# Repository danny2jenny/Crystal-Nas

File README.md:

# Introduction

This is a NAS Case and extention pcb for NanoPi M4.

KiCAD for PCB and FreeCAD for case.

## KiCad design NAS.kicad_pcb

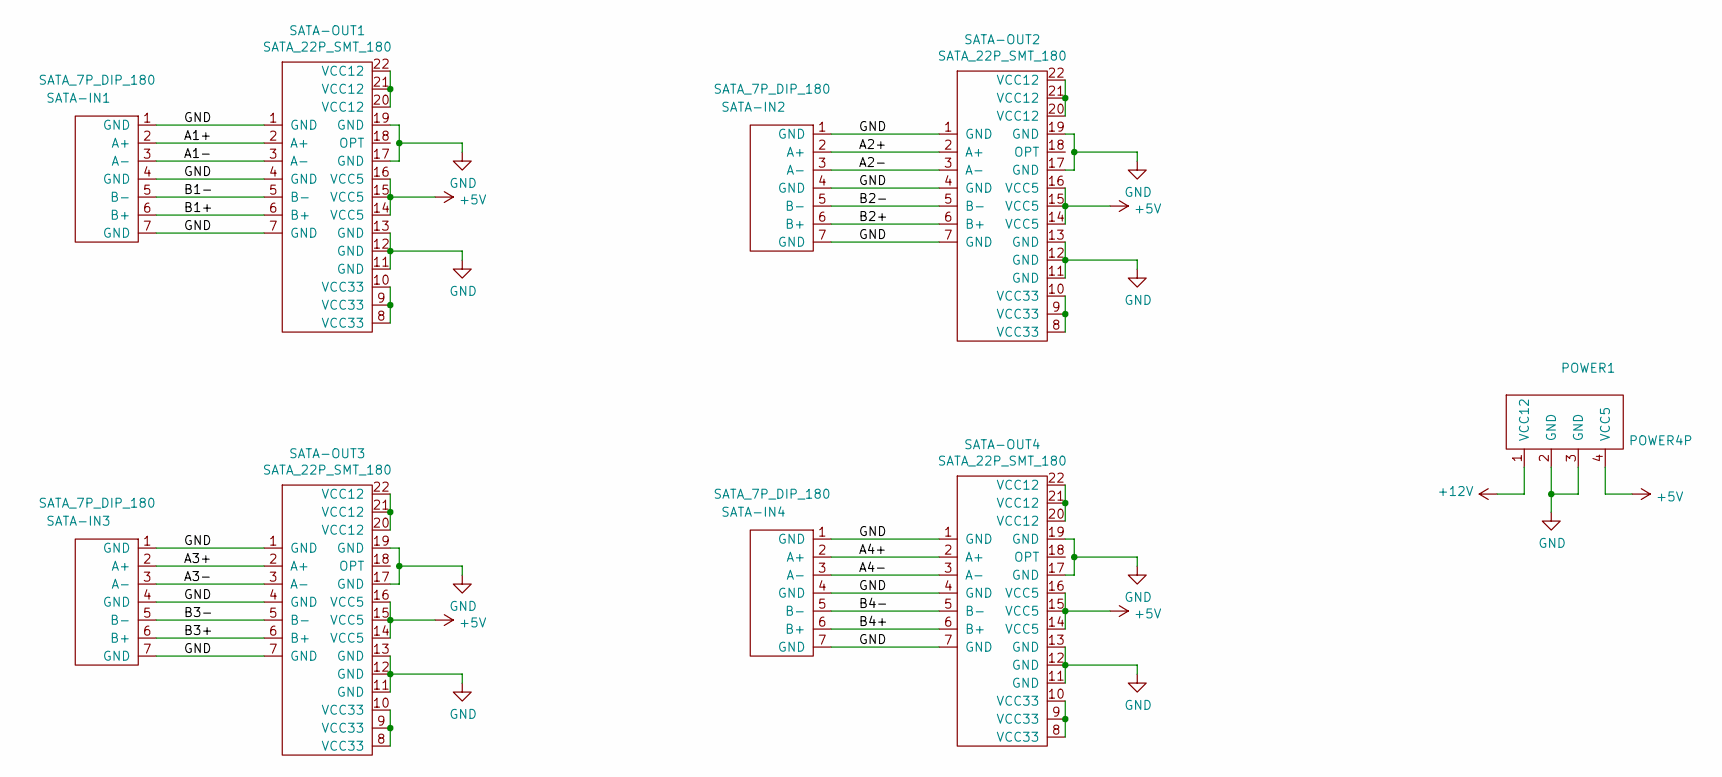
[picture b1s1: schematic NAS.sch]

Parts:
POWER1: POWER4P; Power4P
SATA-IN1, SATA-IN2, SATA-IN3, SATA-IN4: SATA_7P_DIP_180; SATA7PF180
SATA-OUT1, SATA-OUT2, SATA-OUT3, SATA-OUT4: SATA_22P_SMT_180; SATA715F9.1H

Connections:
+5V: POWER1.4 (VCC5), SATA-OUT1.14 (VCC5), SATA-OUT1.15 (VCC5), SATA-OUT1.16 (VCC5), SATA-OUT2.14 (VCC5), SATA-OUT2.15 (VCC5), SATA-OUT2.16 (VCC5), SATA-OUT3.14 (VCC5), SATA-OUT3.15 (VCC5), SATA-OUT3.16 (VCC5), SATA-OUT4.14 (VCC5), SATA-OUT4.15 (VCC5), SATA-OUT4.16 (VCC5)
+12V: POWER1.1 (VCC12)
/A1+: SATA-IN1.2 (A+), SATA-OUT1.2 (A+)
/A1-: SATA-IN1.3 (A-), SATA-OUT1.3 (A-)
/A2+: SATA-IN2.2 (A+), SATA-OUT2.2 (A+)
/A2-: SATA-IN2.3 (A-), SATA-OUT2.3 (A-)
/A3+: SATA-IN3.2 (A+), SATA-OUT3.2 (A+)
/A3-: SATA-IN3.3 (A-), SATA-OUT3.3 (A-)
/A4+: SATA-IN4.2 (A+), SATA-OUT4.2 (A+)
/A4-: SATA-IN4.3 (A-), SATA-OUT4.3 (A-)
/B1+: SATA-IN1.6 (B+), SATA-OUT1.6 (B+)
/B1-: SATA-IN1.5 (B-), SATA-OUT1.5 (B-)
/B2+: SATA-IN2.6 (B+), SATA-OUT2.6 (B+)
/B2-: SATA-IN2.5 (B-), SATA-OUT2.5 (B-)
/B3+: SATA-IN3.6 (B+), SATA-OUT3.6 (B+)
/B3-: SATA-IN3.5 (B-), SATA-OUT3.5 (B-)
/B4+: SATA-IN4.6 (B+), SATA-OUT4.6 (B+)
/B4-: SATA-IN4.5 (B-), SATA-OUT4.5 (B-)
GND: POWER1.2 (GND), POWER1.3 (GND), SATA-IN1.1 (GND), SATA-IN1.4 (GND), SATA-IN1.7 (GND), SATA-IN2.1 (GND), SATA-IN2.4 (GND), SATA-IN2.7 (GND), SATA-IN3.1 (GND), SATA-IN3.4 (GND), SATA-IN3.7 (GND), SATA-IN4.1 (GND), SATA-IN4.4 (GND), SATA-IN4.7 (GND), SATA-OUT1.1 (GND), SATA-OUT1.4 (GND), SATA-OUT1.7 (GND), SATA-OUT1.11 (GND), SATA-OUT1.12 (GND), SATA-OUT1.13 (GND), SATA-OUT1.17 (GND), SATA-OUT1.19 (GND), SATA-OUT2.1 (GND), SATA-OUT2.4 (GND), SATA-OUT2.7 (GND), SATA-OUT2.11 (GND), SATA-OUT2.12 (GND), SATA-OUT2.13 (GND), SATA-OUT2.17 (GND), SATA-OUT2.19 (GND), SATA-OUT3.1 (GND), SATA-OUT3.4 (GND), SATA-OUT3.7 (GND), SATA-OUT3.11 (GND), SATA-OUT3.12 (GND), SATA-OUT3.13 (GND), SATA-OUT3.17 (GND), SATA-OUT3.19 (GND), SATA-OUT4.1 (GND), SATA-OUT4.4 (GND), SATA-OUT4.7 (GND), SATA-OUT4.11 (GND), SATA-OUT4.12 (GND), SATA-OUT4.13 (GND), SATA-OUT4.17 (GND), SATA-OUT4.19 (GND)
unnamed: SATA-OUT1.8 (VCC33), SATA-OUT1.9 (VCC33), SATA-OUT1.10 (VCC33)
unnamed: SATA-OUT1.20 (VCC12), SATA-OUT1.21 (VCC12), SATA-OUT1.22 (VCC12)
unnamed: SATA-OUT2.8 (VCC33), SATA-OUT2.9 (VCC33), SATA-OUT2.10 (VCC33)
unnamed: SATA-OUT2.20 (VCC12), SATA-OUT2.21 (VCC12), SATA-OUT2.22 (VCC12)
unnamed: SATA-OUT3.8 (VCC33), SATA-OUT3.9 (VCC33), SATA-OUT3.10 (VCC33)
unnamed: SATA-OUT3.20 (VCC12), SATA-OUT3.21 (VCC12), SATA-OUT3.22 (VCC12)
unnamed: SATA-OUT4.8 (VCC33), SATA-OUT4.9 (VCC33), SATA-OUT4.10 (VCC33)
unnamed: SATA-OUT4.20 (VCC12), SATA-OUT4.21 (VCC12), SATA-OUT4.22 (VCC12)

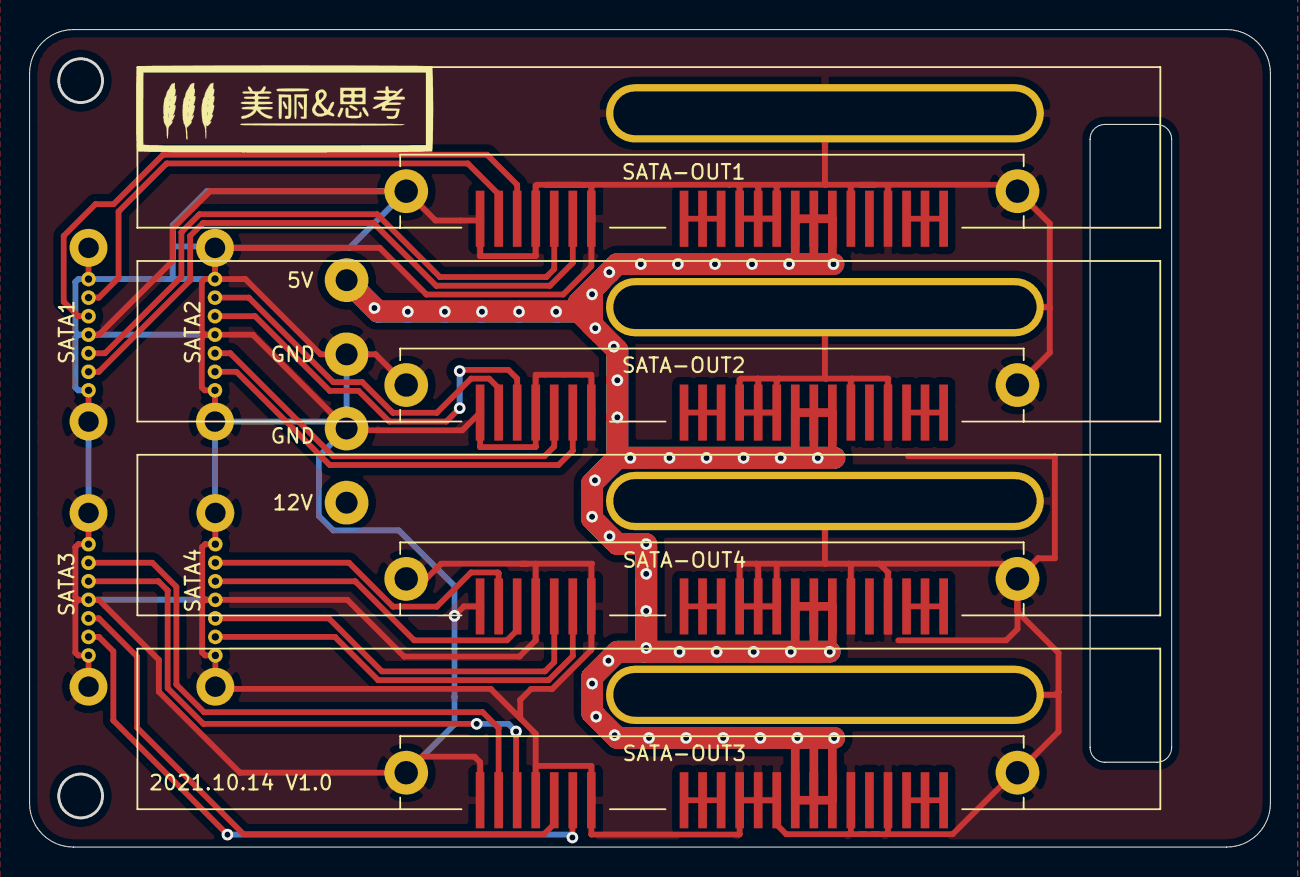
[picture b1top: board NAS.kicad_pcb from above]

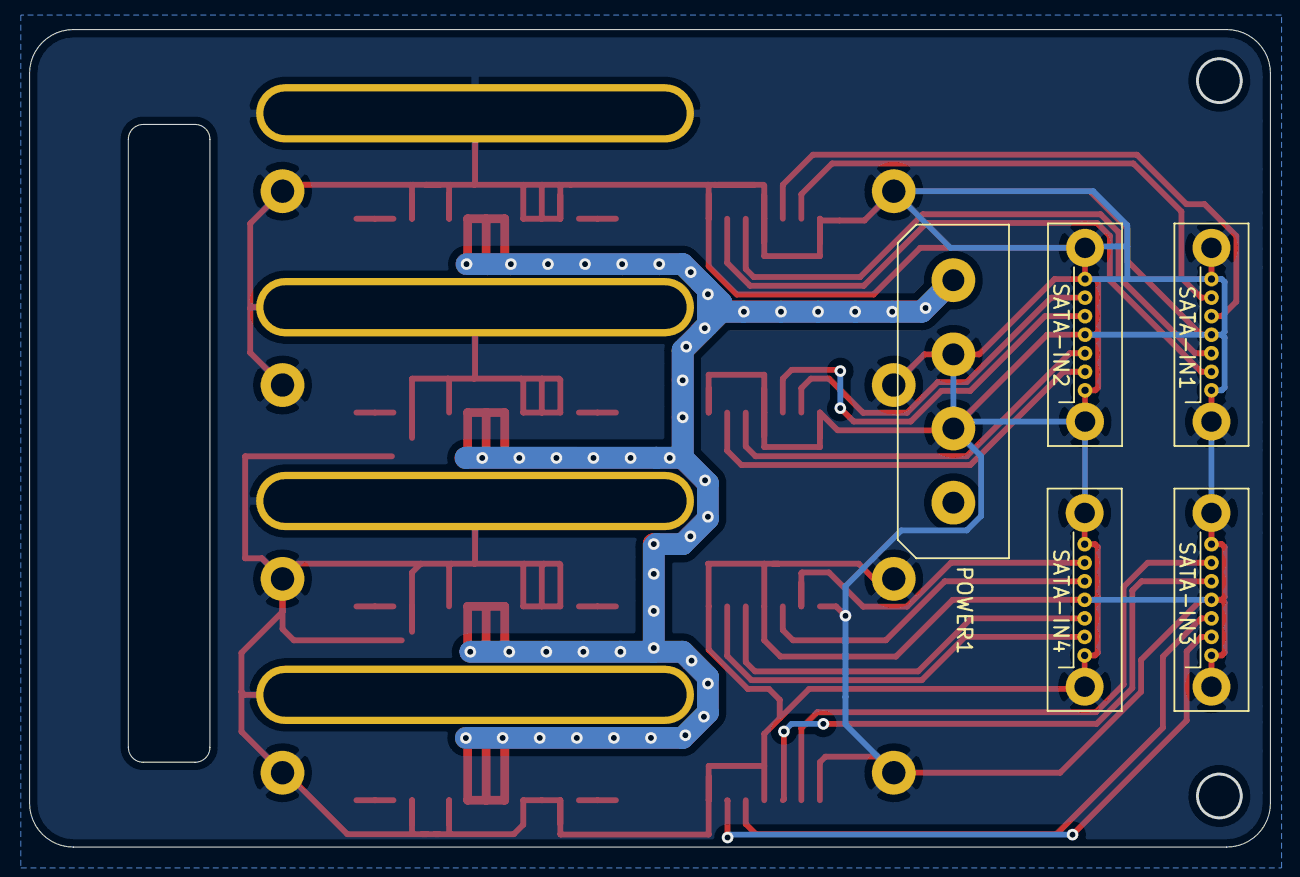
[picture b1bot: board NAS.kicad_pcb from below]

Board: 2 copper layers, 84.8 x 55.8 mm, 9 parts (5 on the bottom side), 26 nets.

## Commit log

2021-10-26 添加图片
